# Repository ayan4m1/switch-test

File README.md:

# SwitchTest

An open-source mechanical keyswitch tester.

## Purpose

To provide a simple, reliable, and fast way to test a batch of keyswitches. You might want to perform batch testing after opening the switch housings in order to lubricate or swap springs. It can also be useful for those who buy and sell keyswitches, to quickly check them after receipt or before shipping.

## Bill of Materials

| Qty | Part                                                                          | Notes                            |
| --- | ----------------------------------------------------------------------------- | -------------------------------- |
| 1   | [10k Ohm Resistor](https://www.amazon.com/dp/B072BL2VX1)                      | Through-hole, 1/4W is sufficient |
| 1   | [PS1240P02CT3](https://www.mouser.com/ProductDetail/810-PS1240P02CT3)         | Piezo buzzer, 4kHz               |
| 1   | [QT Py ESP32-S3](https://www.adafruit.com/product/5426)                       |                                  |
| 1   | [0.96" SSD1306 OLED](https://www.amazon.com/gp/product/B0837DLWVH)            |                                  |
| 1   | [Kailh hotswap socket](https://divinikey.com/products/kailh-hot-swap-sockets) |                                  |
| 4   | [M3 Standoffs](https://www.amazon.com/dp/B098XS4C3D)                          | 8-15mm length                    |
| 8   | M3 Screws                                                                     | 5mm length                       |

You will also need a 3D printed [baseplate](./hardware/baseplate.stl).

Finally, PCBs are available from [this repo](./hardware/tester.brd).

## Schematic

EAGLE schematics are available [here](./hardware/tester.sch).

## Assembly

1. Solder the resistor, OLED, and QT Py to the top of the board.
2. Solder the buzzer and switch socket to the bottom of the board.
3. Attach standoffs to the board.
4. Attach baseplate to the other end of the standoffs.

## Usage

1. Plug the board in to a USB-C cable.
2. Wait for the red LED.
3. Install a switch in the socket and press it. If the light turns green and the buzzer sounds, it is working. Otherwise, it is not.
4. Remove the switch and repeat step 3 for each switch.

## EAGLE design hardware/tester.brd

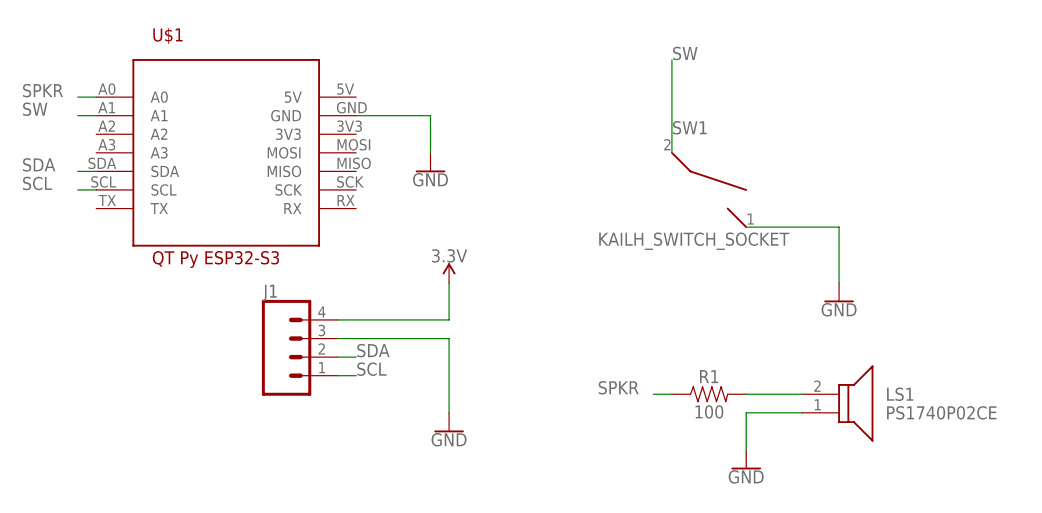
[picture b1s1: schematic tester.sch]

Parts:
J1: CONN_04; 1X04
LS1: PS1740P02CE
R1: 100; AXIAL-0.3
SW1: KAILH_SWITCH_SOCKET; SWITCH_SOCKET
U1: QTPY-ESP32-S3

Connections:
3.3V: J1.4
5V: U1.5V
GND: J1.3, LS1.1 (GND), SW1.1 (2), U1.GND
unnamed: LS1.2 (VCC), R1.P$2 (2)
SCL: J1.1, U1.SCL
SDA: J1.2, U1.SDA
SPKR: R1.P$1 (1), U1.A0
SW: SW1.2 (1), U1.A1

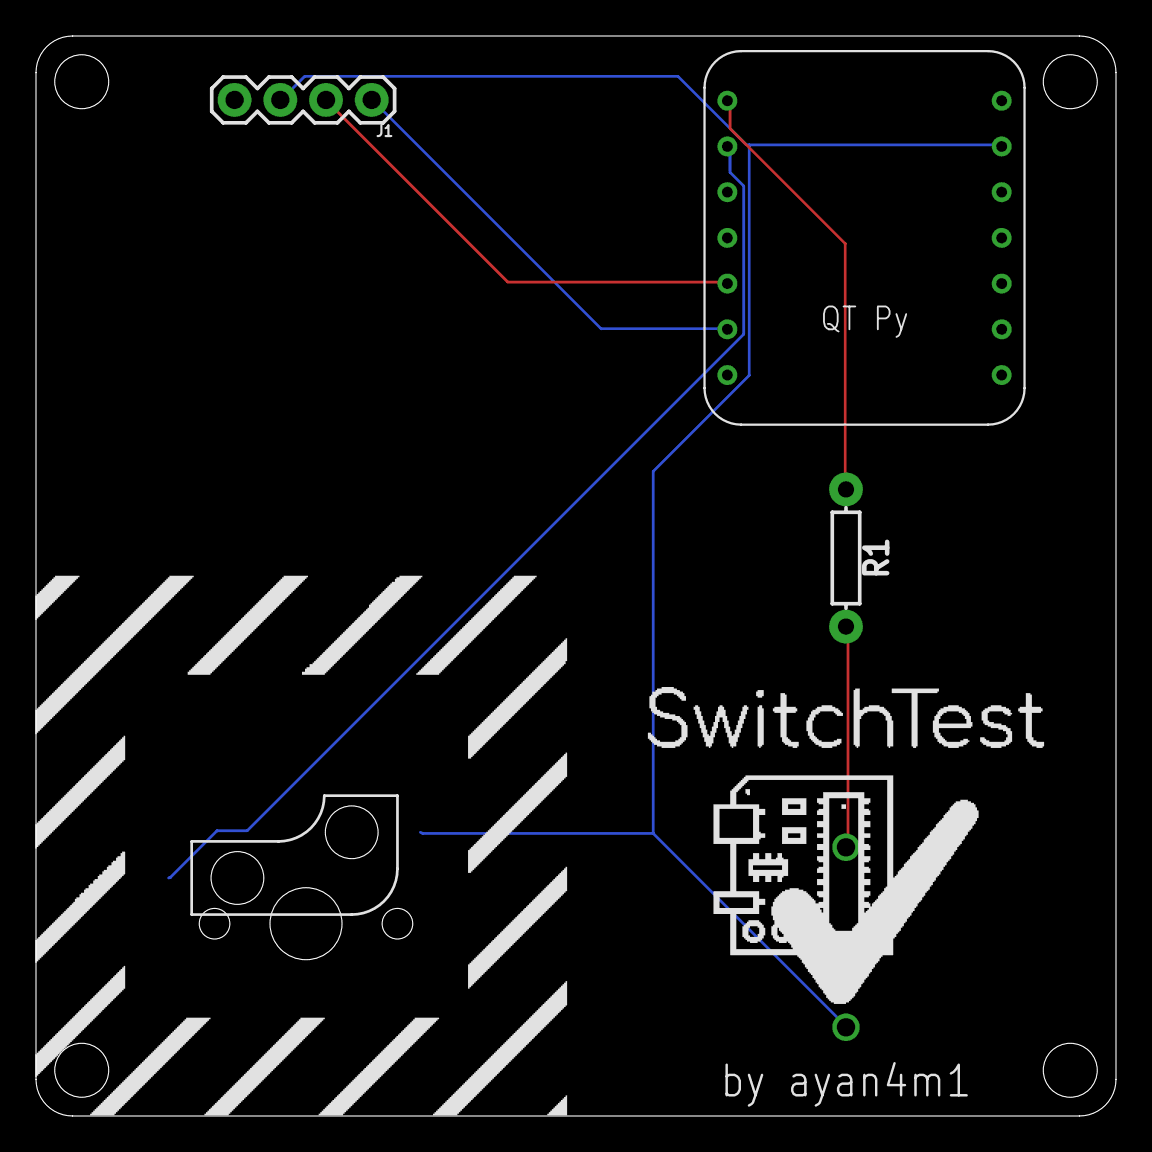
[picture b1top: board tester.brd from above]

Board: 2 copper layers, 60.0 x 60.0 mm, 5 parts (1 on the bottom side), 6 nets.

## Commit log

2022-10-28 initial import
2022-10-28 refactor startup melody code
2022-10-28 add RGB LED functionality
2022-10-28 refactor note code
2022-10-29 add README.md and hardware resources
2022-10-29 simplify color logic for now
2022-10-30 refactor code to modules, start adding OLED display code
2022-10-30 move definitions to cpp files
2022-10-30 toggle buzzer when pressing switch
2022-10-30 fix flicker
2022-10-30 change resistor value to eliminate squeal
2022-11-27 change to st7789/lilygo t-qt
2022-12-22 move to htcw_button, update pin assignments, target t-qt

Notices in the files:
parts and their libraries:
SparkFun-Resistors: Licensing: Creative Commons ShareAlike 4.0 International - https://creativecommons.org/licenses/by-sa/4.0
